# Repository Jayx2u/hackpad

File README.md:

# JayPad
My first PCB design. A macropad made for the YSWS Hack Club event [Hackpad](https://github.com/hackclub/hackpad). Got too many modded Minecraft keybinds...
## Showcase

## PCB

## Case

## Renders

## Acknowledgement
- MX Cherry switches symbol, footprint and model from [sszczep/kicad-libraries/](https://github.com/sszczep/kicad-libraries/tree/master)
- Cute cats from [Neko Atsume](https://www.nekoatsume.com/en/)

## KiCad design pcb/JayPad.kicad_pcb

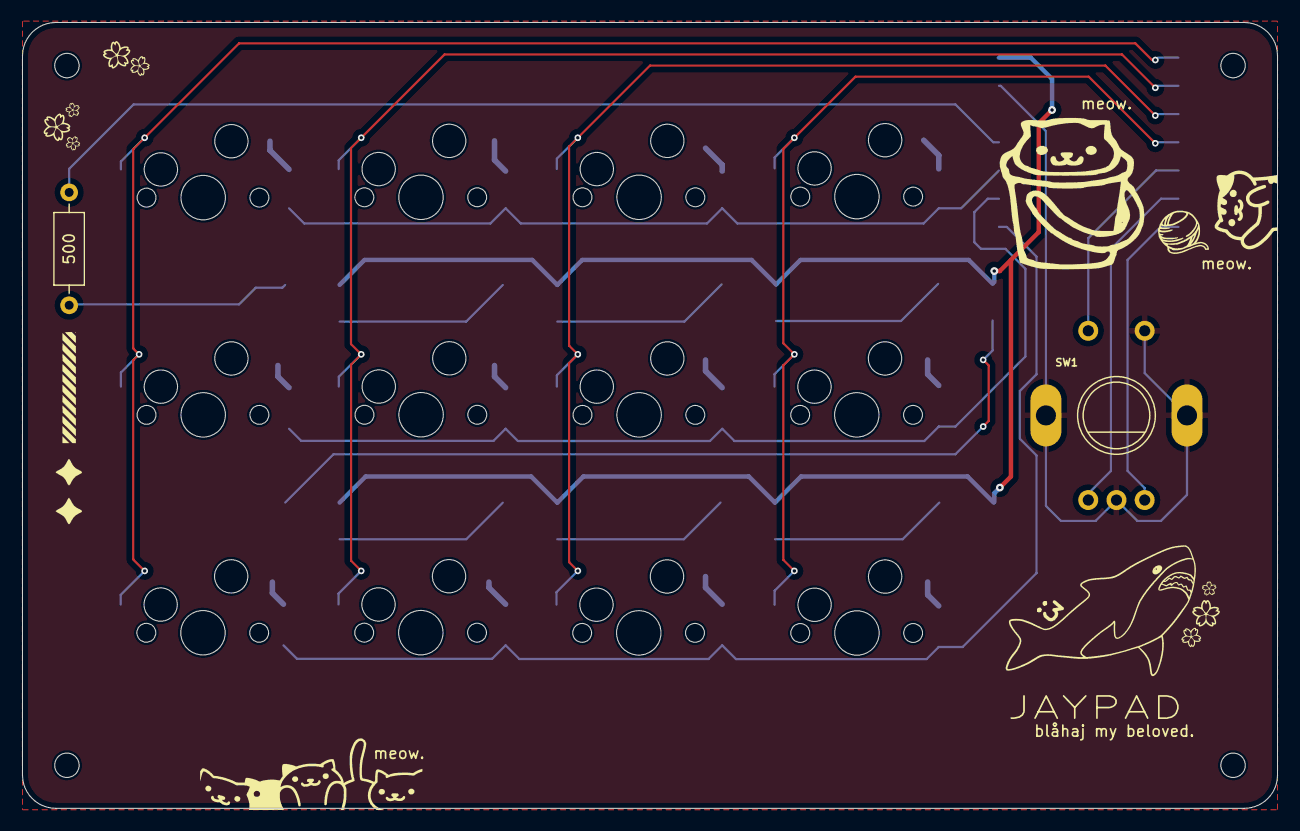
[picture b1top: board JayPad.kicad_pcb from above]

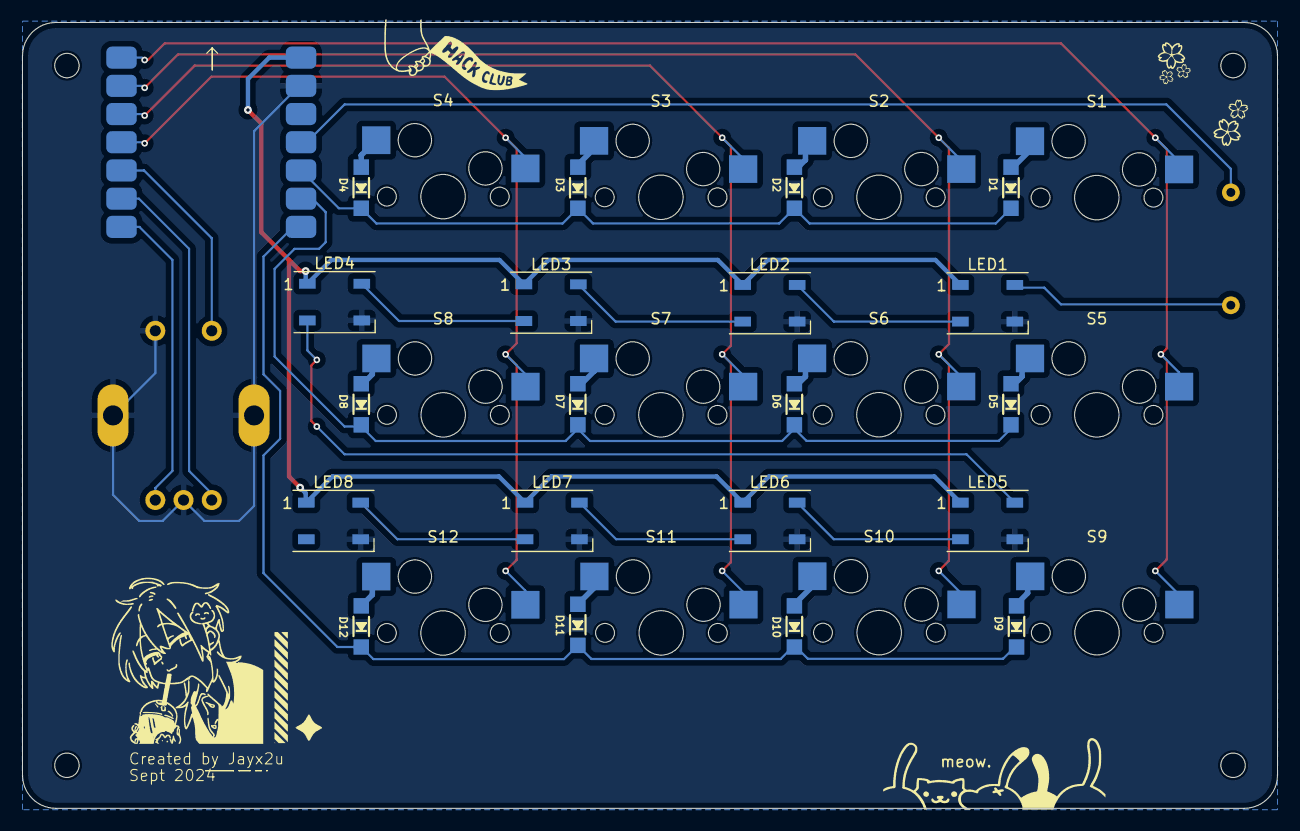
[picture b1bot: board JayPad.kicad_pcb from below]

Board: 2 copper layers, 113.0 x 70.8 mm, 36 parts (21 on the bottom side), 33 nets.

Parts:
:3: LOGO
D1, D2, D3, D4, D5, D6, D7, D8, D9, D10, D11, D12: 1N4148W; MICROBUILDER_SOD-123
LED1, LED2, LED3, LED4, LED5, LED6, LED7, LED8: WS2812B; LED_WS2812B_PLCC4_5.0x5.0mm_P3.2mm
M1: MOUDLE-SEEEDUINO-XIAO; MOUDLE14P-SMD-2.54-21X17.8MM
R1: 500; R_Axial_DIN0207_L6.3mm_D2.5mm_P10.16mm_Horizontal
S1, S2, S3, S4, S5, S6, S7, S8, S9, S10, S11, S12: CherryMX; CherryMX_1.00u_KailhSocket
SW1: PEC11-4215F-S24; ADAFRUIT_ELECTROMECH_PEC11+SWITCH

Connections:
+5V: LED1.1 (VDD), LED2.1 (VDD), LED3.1 (VDD), LED4.1 (VDD), LED5.1 (VDD), LED6.1 (VDD), LED7.1 (VDD), LED8.1 (VDD), M1.14 (5V)
COL0: M1.1 (PA02_A0_D0), S1.1, S5.1, S9.1
COL1: M1.2 (PA4_A1_D1), S2.1, S6.1, S10.1
COL2: M1.3 (PA10_A2_D2), S3.1, S7.1, S11.1
COL3: M1.4 (PA11_A3_D3), S4.1, S8.1, S12.1
DOUT0: LED4.2 (DOUT), LED5.4 (DIN)
ENC_A: M1.6 (PA9_A5_D5_SCL), SW1.P$A
ENC_B: M1.7 (PB08_A6_D6_TX), SW1.P$B
ENC_SW: M1.5 (PA8_A4_D4_SDA), SW1.P$1
GND: LED1.3 (VSS), LED2.3 (VSS), LED3.3 (VSS), LED4.3 (VSS), LED5.3 (VSS), LED6.3 (VSS), LED7.3 (VSS), LED8.3 (VSS), M1.13 (GND), SW1.P$2, SW1.P$C, SW1.P$GND1, SW1.P$GND2
unnamed: D1.A, S1.2
unnamed: D2.A, S2.2
unnamed: D3.A, S3.2
unnamed: D4.A, S4.2
unnamed: D5.A, S5.2
unnamed: D6.A, S6.2
unnamed: D7.A, S7.2
unnamed: D8.A, S8.2
unnamed: D9.A, S9.2
unnamed: D10.A, S10.2
unnamed: D11.A, S11.2
unnamed: D12.A, S12.2
unnamed: LED3.2 (DOUT), LED4.4 (DIN)
unnamed: LED2.2 (DOUT), LED3.4 (DIN)
unnamed: LED1.2 (DOUT), LED2.4 (DIN)
unnamed: LED1.4 (DIN), R1.2
unnamed: LED5.2 (DOUT), LED6.4 (DIN)
unnamed: LED6.2 (DOUT), LED7.4 (DIN)
unnamed: LED7.2 (DOUT), LED8.4 (DIN)
RGB: M1.11 (PA6_A10_D10_MOSI), R1.1
ROW0: D1.C, D2.C, D3.C, D4.C, M1.10 (PA5_A9_D9_MISO)
ROW1: D5.C, D6.C, D7.C, D8.C, M1.9 (PA7_A8_D8_SCK)
ROW2: D9.C, D10.C, D11.C, D12.C, M1.8 (PB09_A7_D7_RX)

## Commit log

2024-09-22 Rename JayPad.kicad_pro to pcb/JayPad.kicad_pro
2024-09-22 Fixed incorrect switch references
2024-09-23 Copper zone set to GND, optimised COL & GND traces
2024-09-23 Fixed GND traces not following DRC
2024-09-23 Changed some trace routes & moved some silkscreen
2024-09-23 Fixed LED cutout shape
2024-09-23 LEDs now using GND copper pour & routed ROW0 which I somehow forgot to do
2024-09-24 Changed from RGB backlight to underglow
2024-09-24 Added some lil silkscreen decor
2024-09-25 Added a bit more decor and changed resistor placement
2024-09-25 Added new images
2024-09-25 hm...
2024-09-25 Added case files
2024-09-25 ah...
2024-09-25 Removed rulers
2024-09-25 Corrected switch plate hole positions
2024-09-26 Initial KMK firmware
2024-09-26 Added RGB and rotary encoder functions
2024-09-26 Added keymap
2024-09-26 Added one lil cat decor
2024-09-26 Updated images and added components list
2024-09-26 Added gerbers
2024-10-05 Added fillets to microcontroller cutout
2024-10-21 Fixed file name
2024-10-21 Added drill files
2025-02-14 Add irl photos of macropad :D
2025-02-14 Compress showcase photos
